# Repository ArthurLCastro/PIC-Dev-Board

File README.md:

# **Plataforma de Desenvolvimento PIC16F628A**

## **Simulação**
- [Arquivos de simulação do circuito completo](./Simulacao-PIC16F628A_Basic_Circuit/)

## **Placa Principal**

<!--  -->

- [Projeto de PCB da Placa Principal](./Projetos_de_PCB-KiCAD/Placa%20Principal/)

## **Placa Auxiliar (LEDs e Botões)**

<!--  -->

- [Projeto de PCB da Placa Auxiliar](./Projetos_de_PCB-KiCAD/Shield%20LEDs%20e%20Botoes/)

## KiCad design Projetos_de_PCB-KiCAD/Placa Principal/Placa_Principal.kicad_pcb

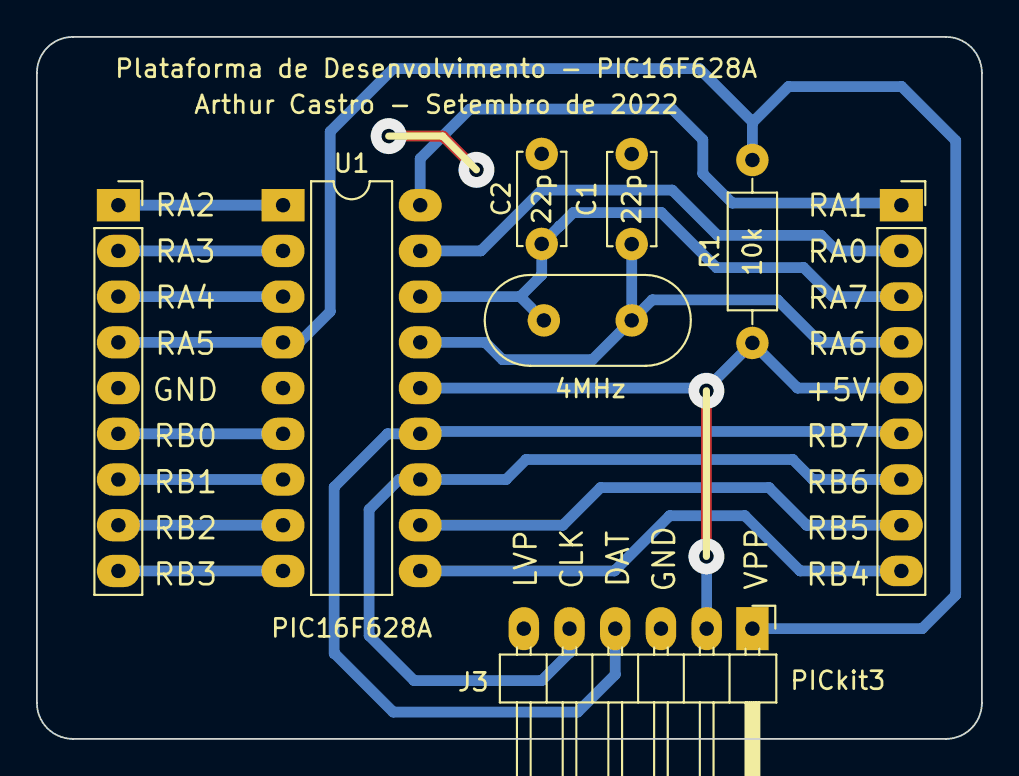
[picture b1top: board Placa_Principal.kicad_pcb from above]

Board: 2 copper layers, 52.5 x 39.0 mm, 8 parts (0 on the bottom side), 18 nets.

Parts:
C1, C2: 22p; C_Disc_D5.0mm_W2.5mm_P5.00mm
J1, J2: Conn_01x09_Female; PinSocket_1x09_P2.54mm_Vertical
J3: PICkit3; PinHeader_1x06_P2.54mm_Horizontal
R1: 10k; R_Axial_DIN0207_L6.3mm_D2.5mm_P10.16mm_Horizontal
U1: PIC16F628A; DIP-18_W7.62mm_LongPads
Y1: 4MHz; Crystal_HC49-4H_Vertical

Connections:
+5V: J2.5, J3.2, R1.1, U1.14 (VDD)
CLK: J2.7, J3.5, U1.12 (RB6/T1OSC0/T1CKI/PGC)
DAT: J2.6, J3.4, U1.13 (RB7/T1OSI/PGD)
GND: C1.2, C2.2, J1.5, J3.3, U1.5 (VSS)
RA0: J2.2, U1.17 (AN0/RA0)
RA1: J2.1, U1.18 (AN1/RA1)
RA2: J1.1, U1.1 (Vref/AN2/RA2)
RA3: J1.2, U1.2 (CMP1/AN3/RA3)
RA4: J1.3, U1.3 (TOCKI/CMP2/RA4)
RA5: J1.4, J3.1, R1.2, U1.4 (~MCLR/Vpp/RA5)
RA6: C1.1, J2.4, U1.15 (CLKOUT/OSC2/RA6), Y1.1
RA7: C2.1, J2.3, U1.16 (CLKIN/OSC1/RA7), Y1.2
RB0: J1.6, U1.6 (RB0/INT)
RB1: J1.7, U1.7 (RB1/RX/DT)
RB2: J1.8, U1.8 (RB2/TX/CK)
RB3: J1.9, U1.9 (RB3/CCP1)
RB4: J2.9, U1.10 (RB4/PGM)
RB5: J2.8, U1.11 (RB5)

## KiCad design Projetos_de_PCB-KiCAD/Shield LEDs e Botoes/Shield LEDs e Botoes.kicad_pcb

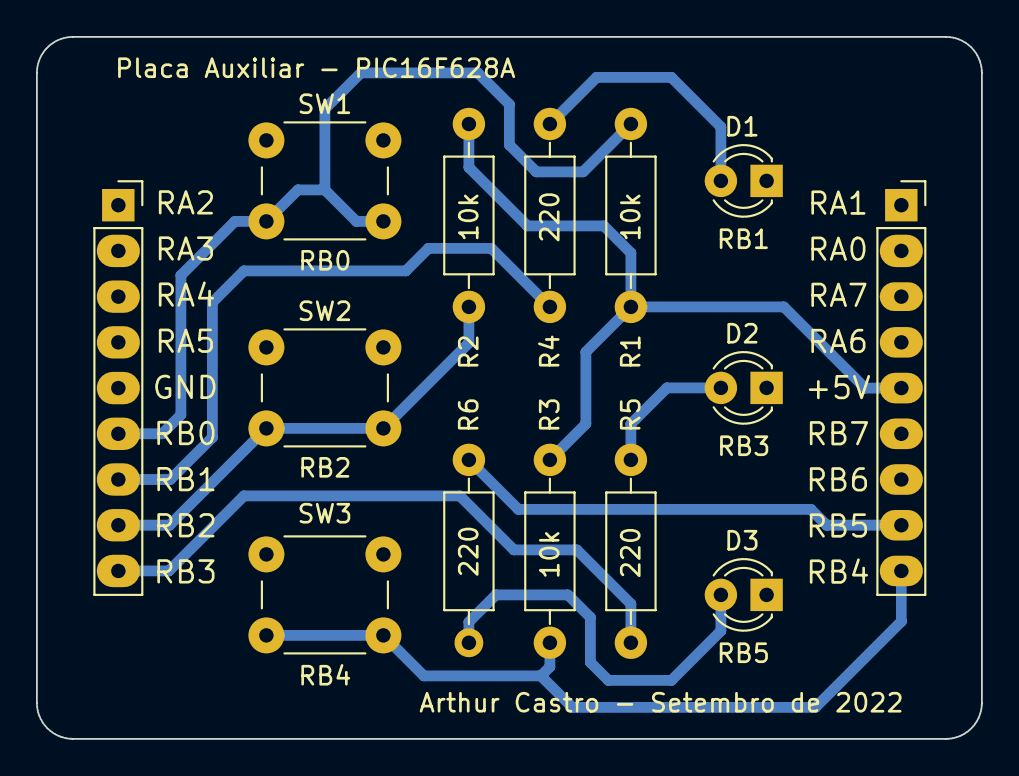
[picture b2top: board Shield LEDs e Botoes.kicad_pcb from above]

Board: 2 copper layers, 52.5 x 39.0 mm, 14 parts (0 on the bottom side), 11 nets.

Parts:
D1: RB1; LED_D3.0mm
D2: RB3; LED_D3.0mm
D3: RB5; LED_D3.0mm
J1, J2: Conn_01x09_Female; PinSocket_1x09_P2.54mm_Vertical
R1, R2, R3: 10k; R_Axial_DIN0207_L6.3mm_D2.5mm_P10.16mm_Horizontal
R4, R5, R6: 220; R_Axial_DIN0207_L6.3mm_D2.5mm_P10.16mm_Horizontal
SW1: RB0; SW_PUSH_6mm_H5mm
SW2: RB2; SW_PUSH_6mm_H5mm
SW3: RB4; SW_PUSH_6mm_H5mm

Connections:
+5V: J2.5, R1.1, R2.1, R3.1
GND: D1.1 (K), D2.1 (K), D3.1 (K), J1.5, SW1.1 (A), SW2.1 (A), SW3.1 (A)
unnamed: D1.2 (A), R4.2
unnamed: D2.2 (A), R5.2
unnamed: D3.2 (A), R6.2
RB0: J1.6, R1.2, SW1.2 (B)
RB1: J1.7, R4.1
RB2: J1.8, R2.2, SW2.2 (B)
RB3: J1.9, R5.1
RB4: J2.9, R3.2, SW3.2 (B)
RB5: J2.8, R6.1

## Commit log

2023-09-05 Upload de arquivos de simulação e projetos de PCBs
